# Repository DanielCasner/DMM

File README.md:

DMM
===

A collection of digital multi-meter designs.

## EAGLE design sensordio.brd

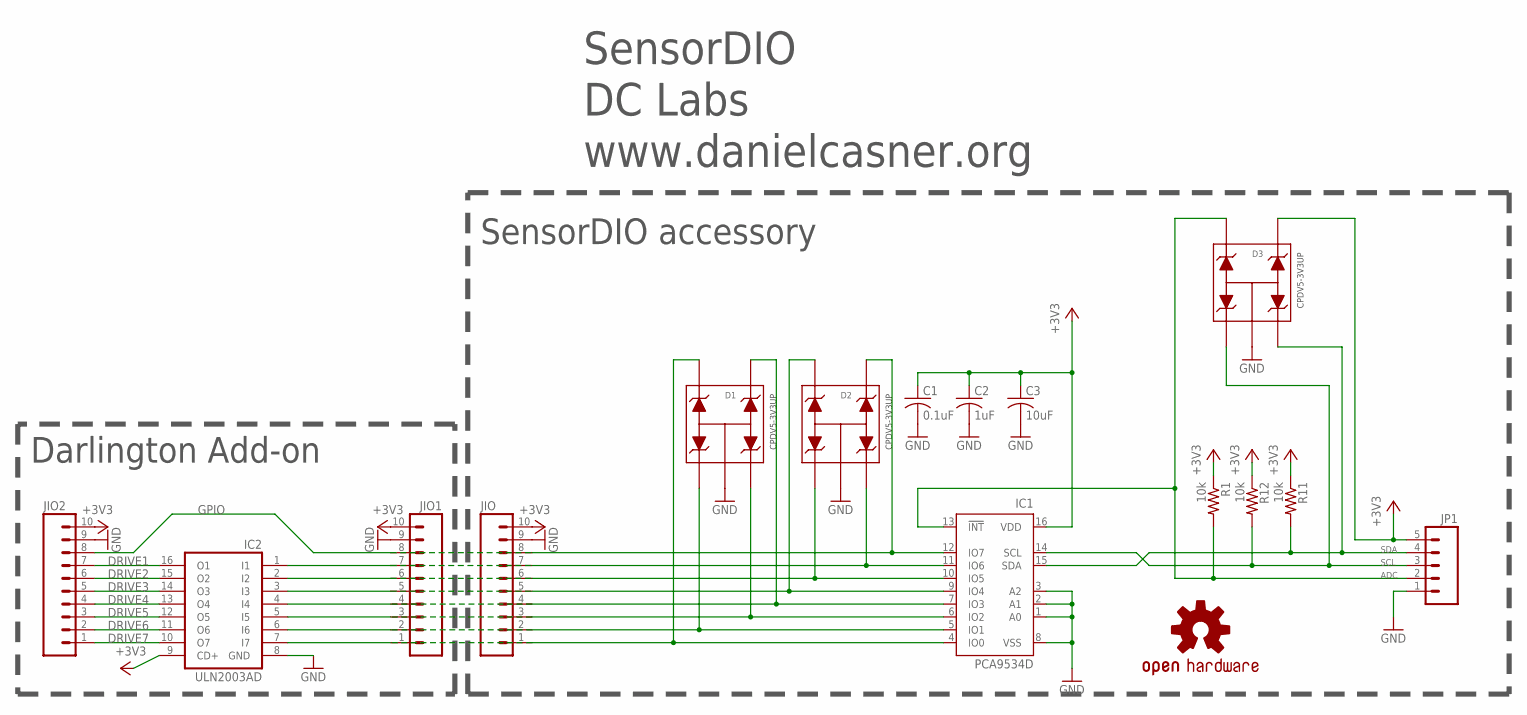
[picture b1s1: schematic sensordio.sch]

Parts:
C1: 0.1uF; C0805
C2: 1uF; C0805
C3: 10uF; C0805
D1, D2, D3: CPDV5-3V3UP; SOT353
IC1: PCA9534D; SO16W
IC2: ULN2003AD; SO16
JIO, JIO1, JIO2: M10; 10P
JP1: M05PTH_LONGPADS; 1X05_LONGPADS
R1, R11, R12: 10k; R0402
U$1: OSHW-LOGOS; OSHW-LOGO-S

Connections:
+3V3: C1.1, C2.1, C3.1, D3.4, IC1.16 (VDD), IC2.9 (CD+), JIO.10, JIO1.10, JIO2.10, JP1.5, R1.1, R11.1, R12.1
ADC: D3.5, IC1.13 (!INT), JP1.2, R1.2
DRIVE1: IC2.16 (O1), JIO2.7
DRIVE2: IC2.15 (O2), JIO2.6
DRIVE3: IC2.14 (O3), JIO2.5
DRIVE4: IC2.13 (O4), JIO2.4
DRIVE5: IC2.12 (O5), JIO2.3
DRIVE6: IC2.11 (O6), JIO2.2
DRIVE7: IC2.10 (O7), JIO2.1
GND: C1.2, C2.2, C3.2, D1.2, D2.2, D3.2, IC1.1 (A0), IC1.2 (A1), IC1.3 (A2), IC1.8 (VSS), IC2.8 (GND), JIO.9, JIO1.9, JIO2.9, JP1.1
GPIO: D2.4, IC1.12 (IO7), JIO.8, JIO1.8, JIO2.8
unnamed: D1.5, IC1.4 (IO0), IC2.7 (I7), JIO.1, JIO1.1
unnamed: D1.1, IC1.5 (IO1), IC2.6 (I6), JIO.2, JIO1.2
unnamed: D1.3, IC1.6 (IO2), IC2.5 (I5), JIO.3, JIO1.3
unnamed: D1.4, IC1.7 (IO3), IC2.4 (I4), JIO.4, JIO1.4
unnamed: D2.5, IC1.9 (IO4), IC2.3 (I3), JIO.5, JIO1.5
unnamed: D2.1, IC1.10 (IO5), IC2.2 (I2), JIO.6, JIO1.6
unnamed: D2.3, IC1.11 (IO6), IC2.1 (I1), JIO.7, JIO1.7
SCL: D3.1, IC1.14 (SCL), JP1.3, R12.2
SDA: D3.3, IC1.15 (SDA), JP1.4, R11.2

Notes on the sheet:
DC Labs
www.danielcasner.org
SensorDIO
SensorDIO accessory
Darlington Add-on

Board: 2 copper layers, 16 parts (0 on the bottom side), 20 nets, no tracks yet.

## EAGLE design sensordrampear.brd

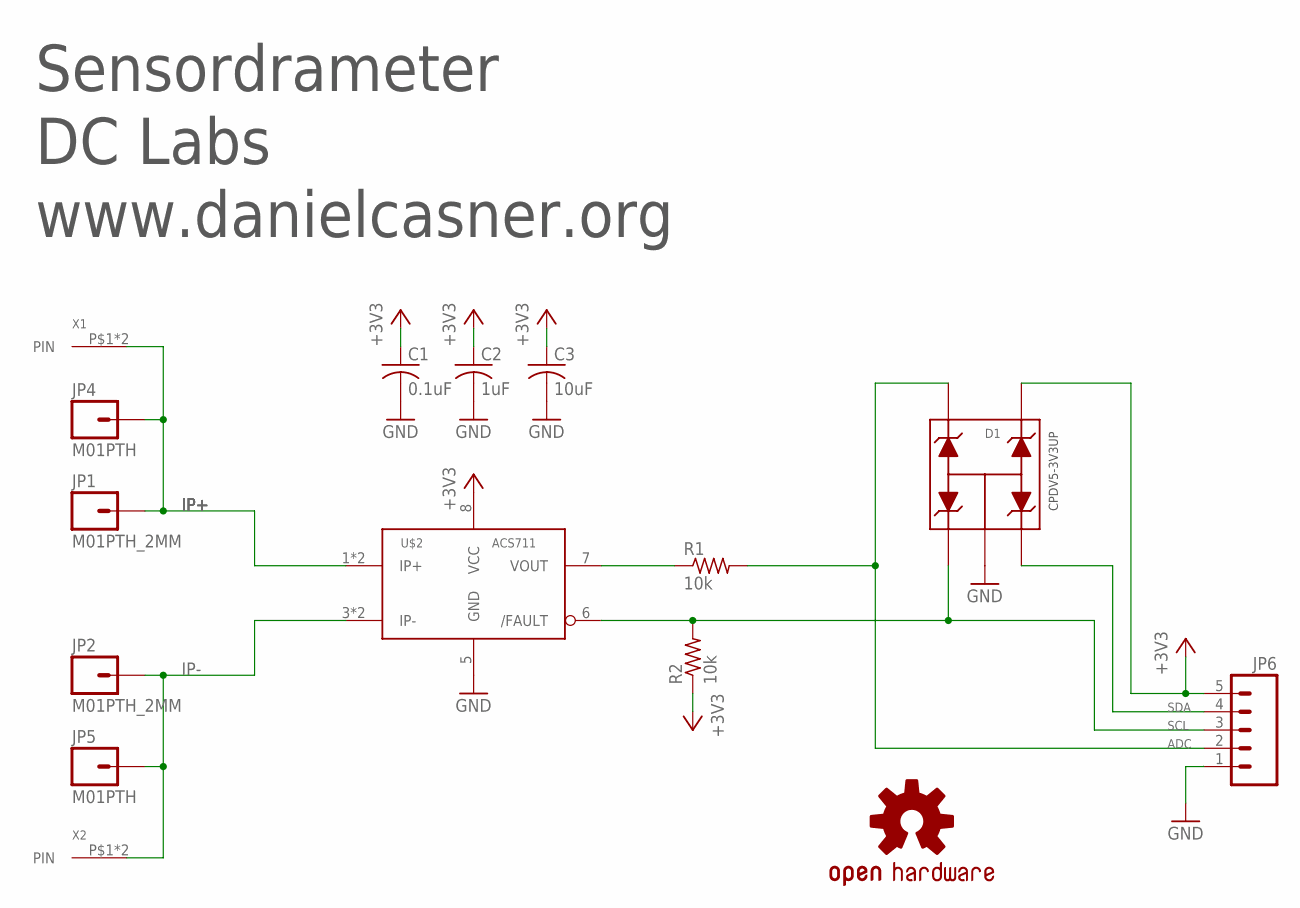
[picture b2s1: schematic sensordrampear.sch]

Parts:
C1: 0.1uF; C0805
C2: 1uF; C0805
C3: 10uF; C0805
D1: CPDV5-3V3UP; SOT353
JP1, JP2: M01PTH_2MM; 1X01_2MM
JP4, JP5: M01PTH; 1X01
JP6: M05PTH_LONGPADS; 1X05_LONGPADS
R1, R2: 10k; R0402
U$1: OSHW-LOGOS; OSHW-LOGO-S
U$2: ACS711; SO8
X1, X2: 606X

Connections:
+3V3: C1.1, C2.1, C3.1, D1.4, JP6.5, R2.1, U$2.8 (VCC)
ADC: D1.5, JP6.2, R1.2
GND: C1.2, C2.2, C3.2, D1.2, JP6.1, U$2.5 (GND)
IP+: JP1.1, JP4.1, U$2.1 (IP+), U$2.2 (IP+), X1.P$1, X1.P$2
IP-: JP2.1, JP5.1, U$2.3 (IP-), U$2.4 (IP-), X2.P$1, X2.P$2
unnamed: R1.1, U$2.7 (VOUT)
SCL: D1.1, JP6.3, R2.2, U$2.6 (/FAULT)
SDA: D1.3, JP6.4

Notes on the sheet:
DC Labs
www.danielcasner.org
Sensordrameter

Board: 2 copper layers, 15 parts (0 on the bottom side), 8 nets, no tracks yet.

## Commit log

2012-07-28 Add first cut at SensordrOHM DMM
    SensordrOHM DMM is an accessory for the sensor drone hardware.
    http://www.sensorcon.com/android_sensors/
2012-07-29 Add SensordrAMPEAR and sensor drone audio jack schematics.
    More rough plans for Sensordrone accessories.
2012-07-30 Add GPIO extension for sensordrone.
2012-08-03 Add add-on add-on for SensordrIO
2012-08-03 Add pin signal labels
2012-08-03 Add boxes around components
2012-08-03 Add very rough beginning of a layout for SensorDIO
2012-08-03 Whoops, missing from previous.

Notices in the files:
parts and their libraries:
SparkFun-Connectors: Licensing: CC v3.0 Share-Alike You are welcome to use this library for commercial purposes.
